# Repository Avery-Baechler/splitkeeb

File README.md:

# Split Keyboard
### Overview
1. Kailh Choc switches ([Link](https://mechanicalkeyboards.com/shop/index.php?l=product_detail&p=6337 "Link"))
2. Work Louder keycaps ([Link](https://worklouder.cc/keycaps/ "Link"))
3. Aduino Pro micro
4. PCB fabricated with JCLPCB
5. 3d printed case 

#### Pinout for Atmega32u4 
```
Row : 0 : D15 —> B1
Row : 1 : D14 —>  B3
Row : 2 : D16 —> B2
Row : 3 : D10 —> B6
Col : 0 : D2 —> D1
Col : 1 : D3 —> D0
Col : 2 : D4 —> D4
Col : 3 : D5 —> C6
Col : 4 : D6 —> D7
Col : 5 : D7 —> E6
Col : 6 : D8 —> B4
Col : 7 : D9 —> B5
Col : 8 : A0 —> F7
Col : 9 : A1 —> F6
Col : 10 : A2 —> F5
Col : 11 : A3 —> F4

```

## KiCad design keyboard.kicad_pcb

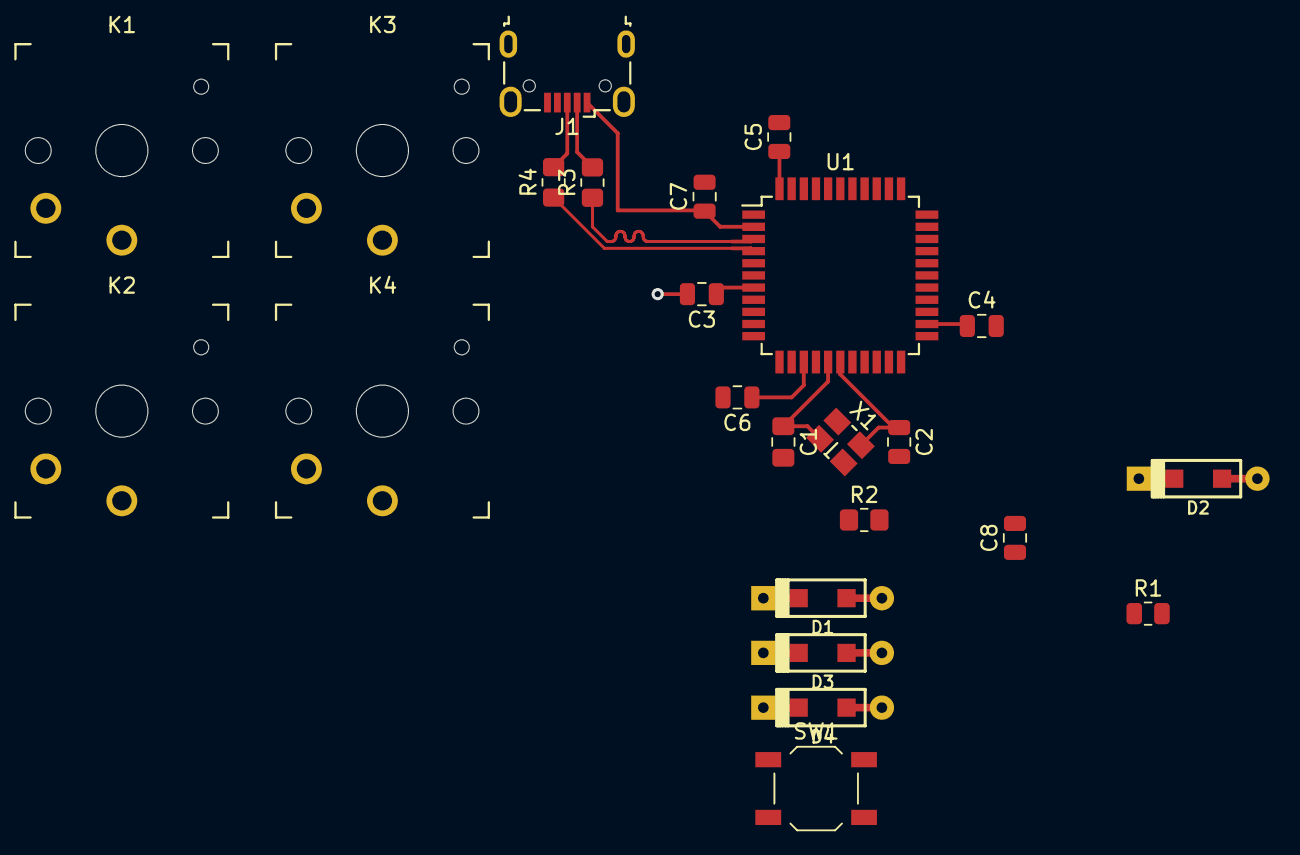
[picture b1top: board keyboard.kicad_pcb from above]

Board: 2 copper layers, 24 parts (0 on the bottom side), 20 nets.

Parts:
C1: 22P; C_0805_2012Metric_Pad1.18x1.45mm_HandSolder
C2: 22P; C_0805_2012Metric
C3, C4, C5, C6: 0.1u; C_0805_2012Metric
C7: 4.7u; C_0805_2012Metric
C8: 1u; C_0805_2012Metric
D1, D2, D3, D4: D; D_SOD123_axial
J1: USB_mini_micro_B; USB_Micro-B_Wuerth_629105150521
K1, K2, K3, K4: KEYSW; SW_PG1350
R1: 10k; R_0805_2012Metric
R2: 10k; R_0805_2012Metric_Pad1.20x1.40mm_HandSolder
R3, R4: 22; R_0805_2012Metric_Pad1.20x1.40mm_HandSolder
SW1: SW_PUSH; SW_SPST_TL3342
U1: ATMEGA32U4; TQFP-44_10x10mm_Pitch0.8mm
X1: XTAL_GND; crystal_FA238-TSX3225

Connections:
+5V: C1.2, C2.2, X1.3
/DN: R3.1, U1.3
/DP: R4.1, U1.4
/col0: K1.1, K2.1, U1.39
/col1: K3.1, K4.1, U1.38
/row0: D1.1, D3.1, U1.41
/row1: D2.1, D4.1, U1.40
GND: C3.2, C4.2, C5.2, C6.2, C7.2, C8.2, J1.5, J1.6, R2.1, SW1.1, U1.5, U1.15, U1.23, U1.35, U1.43
unnamed: C1.1, U1.16, X1.1
unnamed: C2.1, U1.17, X1.2
unnamed: C8.1, U1.6
unnamed: D1.2, K1.2
unnamed: D2.2, K2.2
unnamed: D3.2, K3.2
unnamed: D4.2, K4.2
unnamed: J1.2, R3.2
unnamed: J1.3, R4.2
unnamed: R1.1, SW1.2, U1.13
unnamed: R2.2, U1.33
VCC: C3.1, C4.1, C5.1, C6.1, C7.1, J1.1, R1.2, U1.2, U1.7, U1.14, U1.24, U1.34, U1.44

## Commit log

2022-11-03 Update
    Adding files
2022-11-03 Update Photo
